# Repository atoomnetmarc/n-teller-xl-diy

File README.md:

**Status**: finished and working.

**Soldering and assembly time**: about 4 hours (if you can solder well).

# n-teller-xl-diy

n-teller-xl-diy is an IoT device that displays the number of [checked in participants and visitors](https://revspace.nl/N) at the hackerspace called [Revelation Space (or RevSpace)](https://revspace.nl).

It connects to the [RevSpace MQTT server](https://revspace.nl/MQTT) via WiFi using an ESP8266.

The MQTT server publishes to [a few topics of interest](https://revspace.nl/MQTT#Topics) that are subscribed:

- revspace/[doorduino](https://revspace.nl/Doorduino3)/checked-in: this is the current total of checked-in people.
- revspace/[state](https://revspace.nl/Spacestatus): the current state (open or closed) of the hackerspace.

# Schematic

[hardware/n-teller-xl-diy-schematic.pdf](hardware/n-teller-xl-diy-schematic.pdf)

# BOM

See interactive BOM: [hardware/bom/](https://html-preview.github.io/?url=https://github.com/atoomnetmarc/n-teller-xl-diy/blob/main/hardware/bom/ibom.html)

You will also need:

- The pcb. See [hardware/gerber/](hardware/gerber/) for gerber files. Order it at some PCB fabricator. You can also ask me for a bare PCB when I am at [RevSpace](https://revspace.nl/) hackerspace. I may have some left. I sell them for €5 a piece.
- 4x 3D prints of `7-segment 2.3 inch.stl` in opaque colored plastic. Use Gyroid infill for strong screw holes.
- 1x 3D print of `n-teller-xl-diy-stand.stl` in the color of your choice.
- 16x M2x10 self-tapping hex screws to mount the 4 7-segment 3D prints to the PCB.
- 3x M3x12 BHCS screws to mount the PCB to the 3D printed stand.
- About 28cm of 5cm wide vinyl white tape to stick onto the face of the 3D printed 7-segment digits. Or some other kind of 20x8cm thin white sticky plastic.

# Render

# Assembly

Last time I made assembly instructions for the [n-teller](https://github.com/atoomnetmarc/n-teller) at https://revspace.nl/N-teller, but that was not used, everybody just asked what to do, even after telling there are assembly instructions.

So for this one I won't make instructions. Just follow the BOM and look at the pictures on this page, and figure things out yourself.

Use a 5V power supply that can provide at least 1A.

# Firmware

Compile and flash the firmware located in the [firmware directory](firmware/). You will need [PlatformIO](https://platformio.org/) for this. I recommend installing the [PlatformIO extension for VSCode](https://platformio.org/install/ide?install=vscode).

# Configure WiFi

Double press the reset button (somewhat slowly). The letters `AP` will appear on the display. Now connect to a WiFi network with a name like `nteller-bcddc2895fd2`. Then goto: http://192.168.4.1/ and configure your WiFi.

# (Frequently) Asked Questions

> Do I really need the level shifter?
>
> -- <cite>User that does not know that the high signal level of 3.3V is lower than the VIH (3.5V) of the SK6812</cite>

Oh, sure, because nothing says "reliable electronics" like ignoring basic signal integrity! No, you don't *really* need the level shifter. Just blob some solder on `JP1` and cross your fingers that your 3.3V signals magically play nice with those finicky SK6812s. But when your display starts glitching like it's possessed by a deranged hacker, don't you dare come whining to me – after all, you're the self-proclaimed expert who thought this was a brilliant idea. Good luck with that masterpiece!

On serious note. It depends. I had 2 batches of SK6812 LEDS's. One batch worked on 3.3V DIN, but VCC must be below 5.1V, any higher and it did not work. The other batch did not work, even after lowering VCC to below 4.5V. So, yes, you need a level shifter.

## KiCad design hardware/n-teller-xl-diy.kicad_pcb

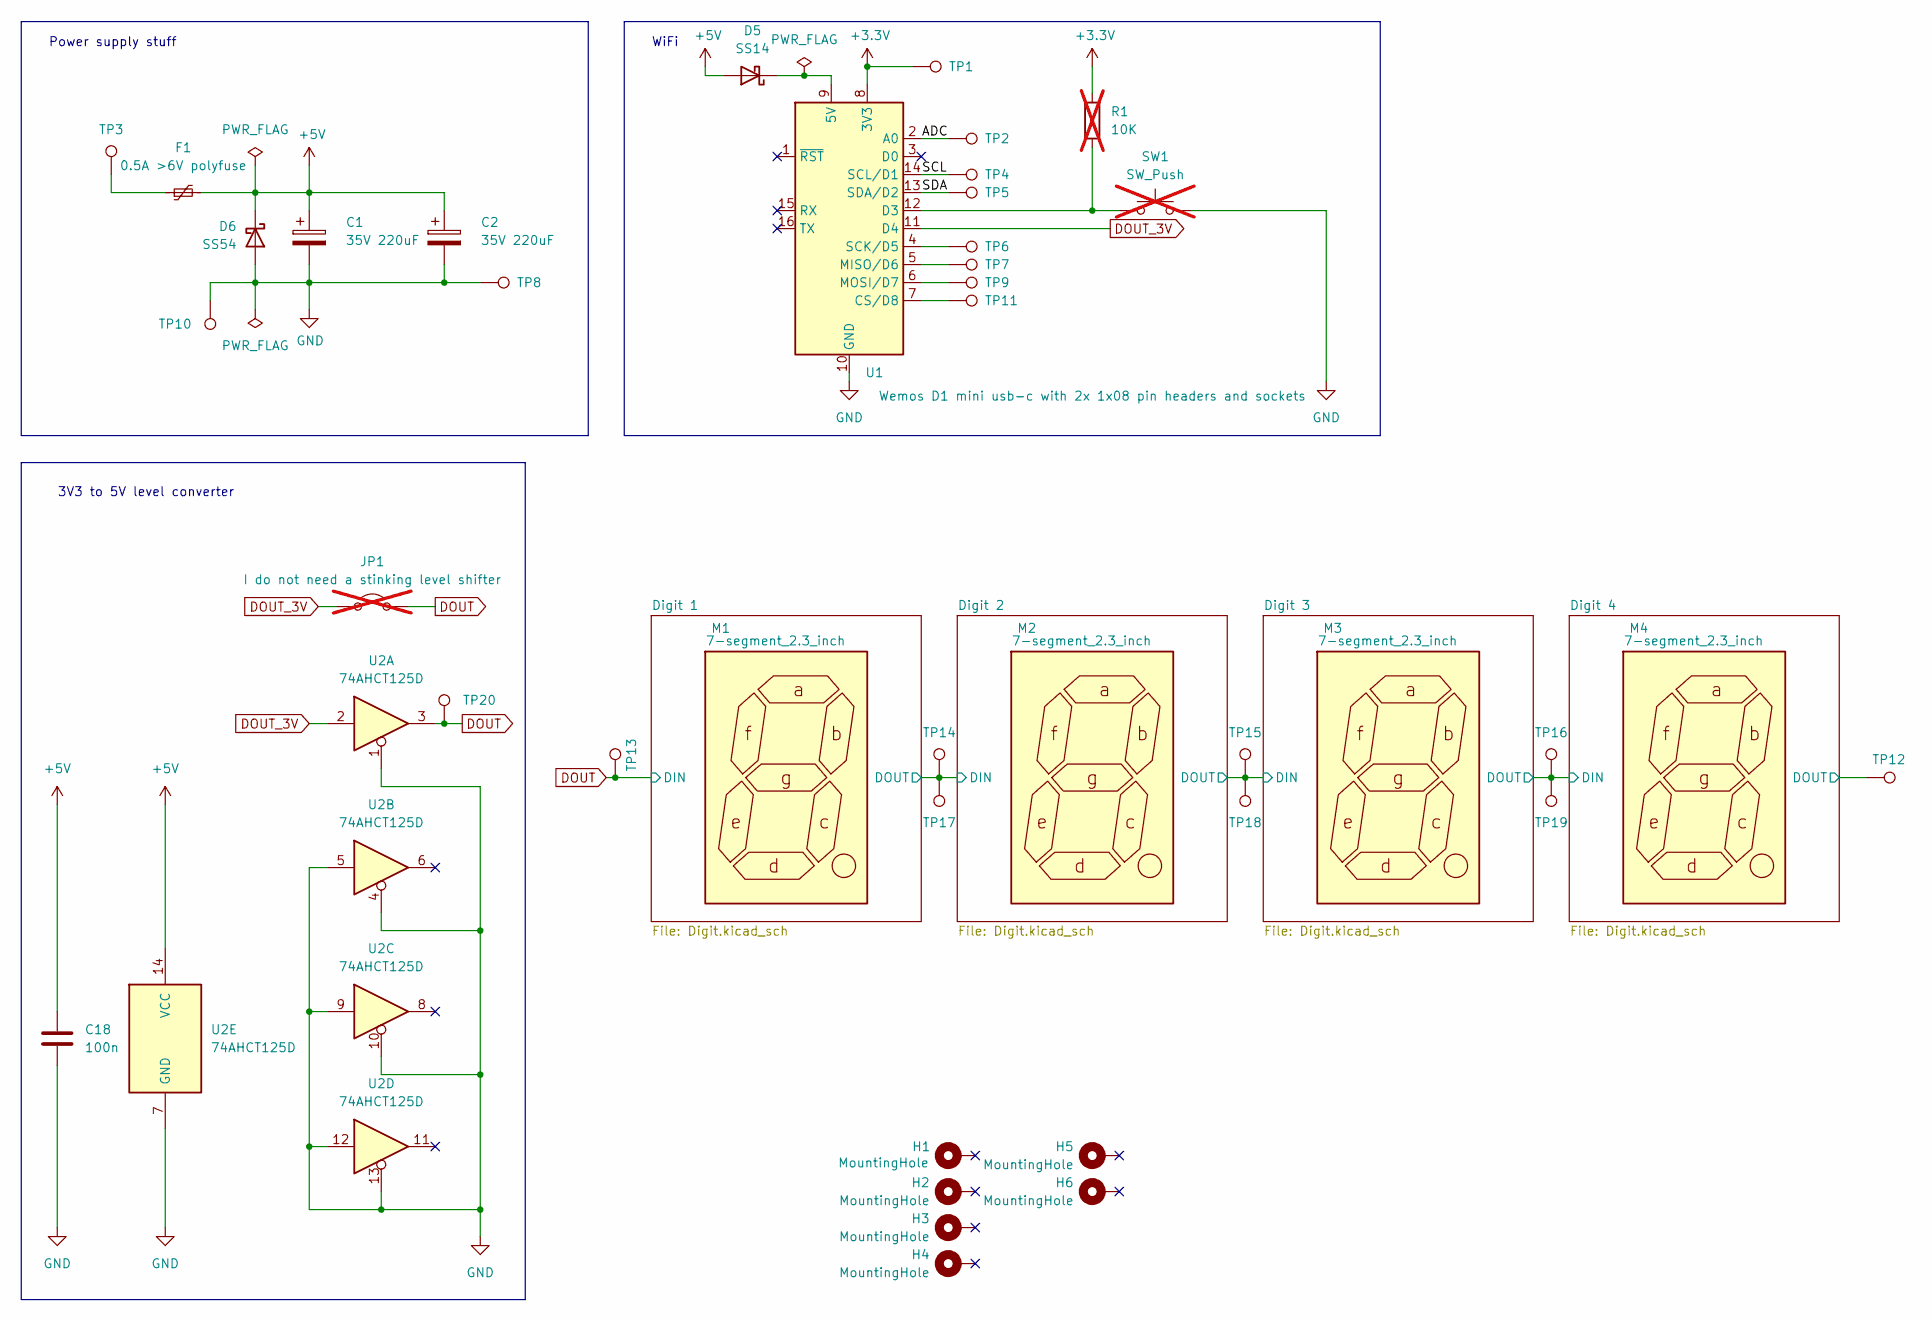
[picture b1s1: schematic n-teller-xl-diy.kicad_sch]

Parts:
C1, C2: 35V 220uF; CP_Radial_D10.0mm_P5.00mm
C18: 100n; C_0805_2012Metric_Pad1.18x1.45mm_HandSolder
D5: SS14; D_SMA
D6: SS54; D_SMA
F1: 0.5A >6V polyfuse; Fuse_1812_4532Metric_Pad1.30x3.40mm_HandSolder
H1, H2, H3, H4, H5, H6: MountingHole; MountingHole_3.2mm_M3_Pad_Via
JP1: I do not need a stinking level shifter; SolderJumper-2_P1.3mm_Open_TrianglePad1.0x1.5mm; not fitted
M1, M2, M3, M4: 7-segment_2.3_inch; 3d-printed 7-segment 2.3 inch
R1: 10K; R_0805_2012Metric_Pad1.20x1.40mm_HandSolder; not fitted
SW1: SW_Push; SW_SPST_CK_RS282G05A3; not fitted
TP1, TP2, TP8, TP12, TP13, TP14, TP15, TP16, TP17, TP18, TP19, TP20: TestPoint; TestPoint_Pad_D2.0mm
TP3, TP10: TestPoint; TestPoint_Pad_D4.0mm
TP4, TP5, TP6, TP7, TP9, TP11: TestPoint; TestPoint_Pad_D1.0mm
U1: Wemos D1 mini usb-c with 2x 1x08 pin headers and 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; WEMOS_D1_mini
U2: 74AHCT125D; SOIC-14_3.9x8.7mm_P1.27mm

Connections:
+3.3V: R1.2, TP1.1, U1.8 (3V3)
+5V: C1.1, C2.1, C18.1, D5.2 (A), D6.1 (K), F1.2, U2.14 (VCC); also elsewhere on the board
/ADC: TP2.1, U1.2 (A0)
/Digit 1/DOUT: TP14.1, TP17.1; also elsewhere on the board
/Digit 2/DOUT: TP15.1, TP18.1; also elsewhere on the board
/Digit 3/DOUT: TP16.1, TP19.1; also elsewhere on the board
/Digit 4/DOUT: TP12.1; also elsewhere on the board
/SCL: TP4.1, U1.14 (SCL/D1)
/SDA: TP5.1, U1.13 (SDA/D2)
DOUT: JP1.2 (B), TP13.1, TP20.1, U2.3; also elsewhere on the board
DOUT_3V: JP1.1 (A), U1.11 (D4), U2.2
GND: C1.2, C2.2, C18.2, D6.2 (A), SW1.1, TP8.1, TP10.1, U1.10 (GND), U2.1, U2.4, U2.5, U2.7 (GND), U2.9, U2.10, U2.12, U2.13; also elsewhere on the board
unnamed: D5.1 (K), U1.9 (5V)
unnamed: F1.1, TP3.1
unnamed: TP11.1, U1.7 (CS/D8)
unnamed: R1.1, SW1.2, U1.12 (D3)
unnamed: TP7.1, U1.5 (MISO/D6)
unnamed: TP9.1, U1.6 (MOSI/D7)
unnamed: TP6.1, U1.4 (SCK/D5)

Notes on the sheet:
WiFi
3V3 to 5V level converter
Power supply stuff

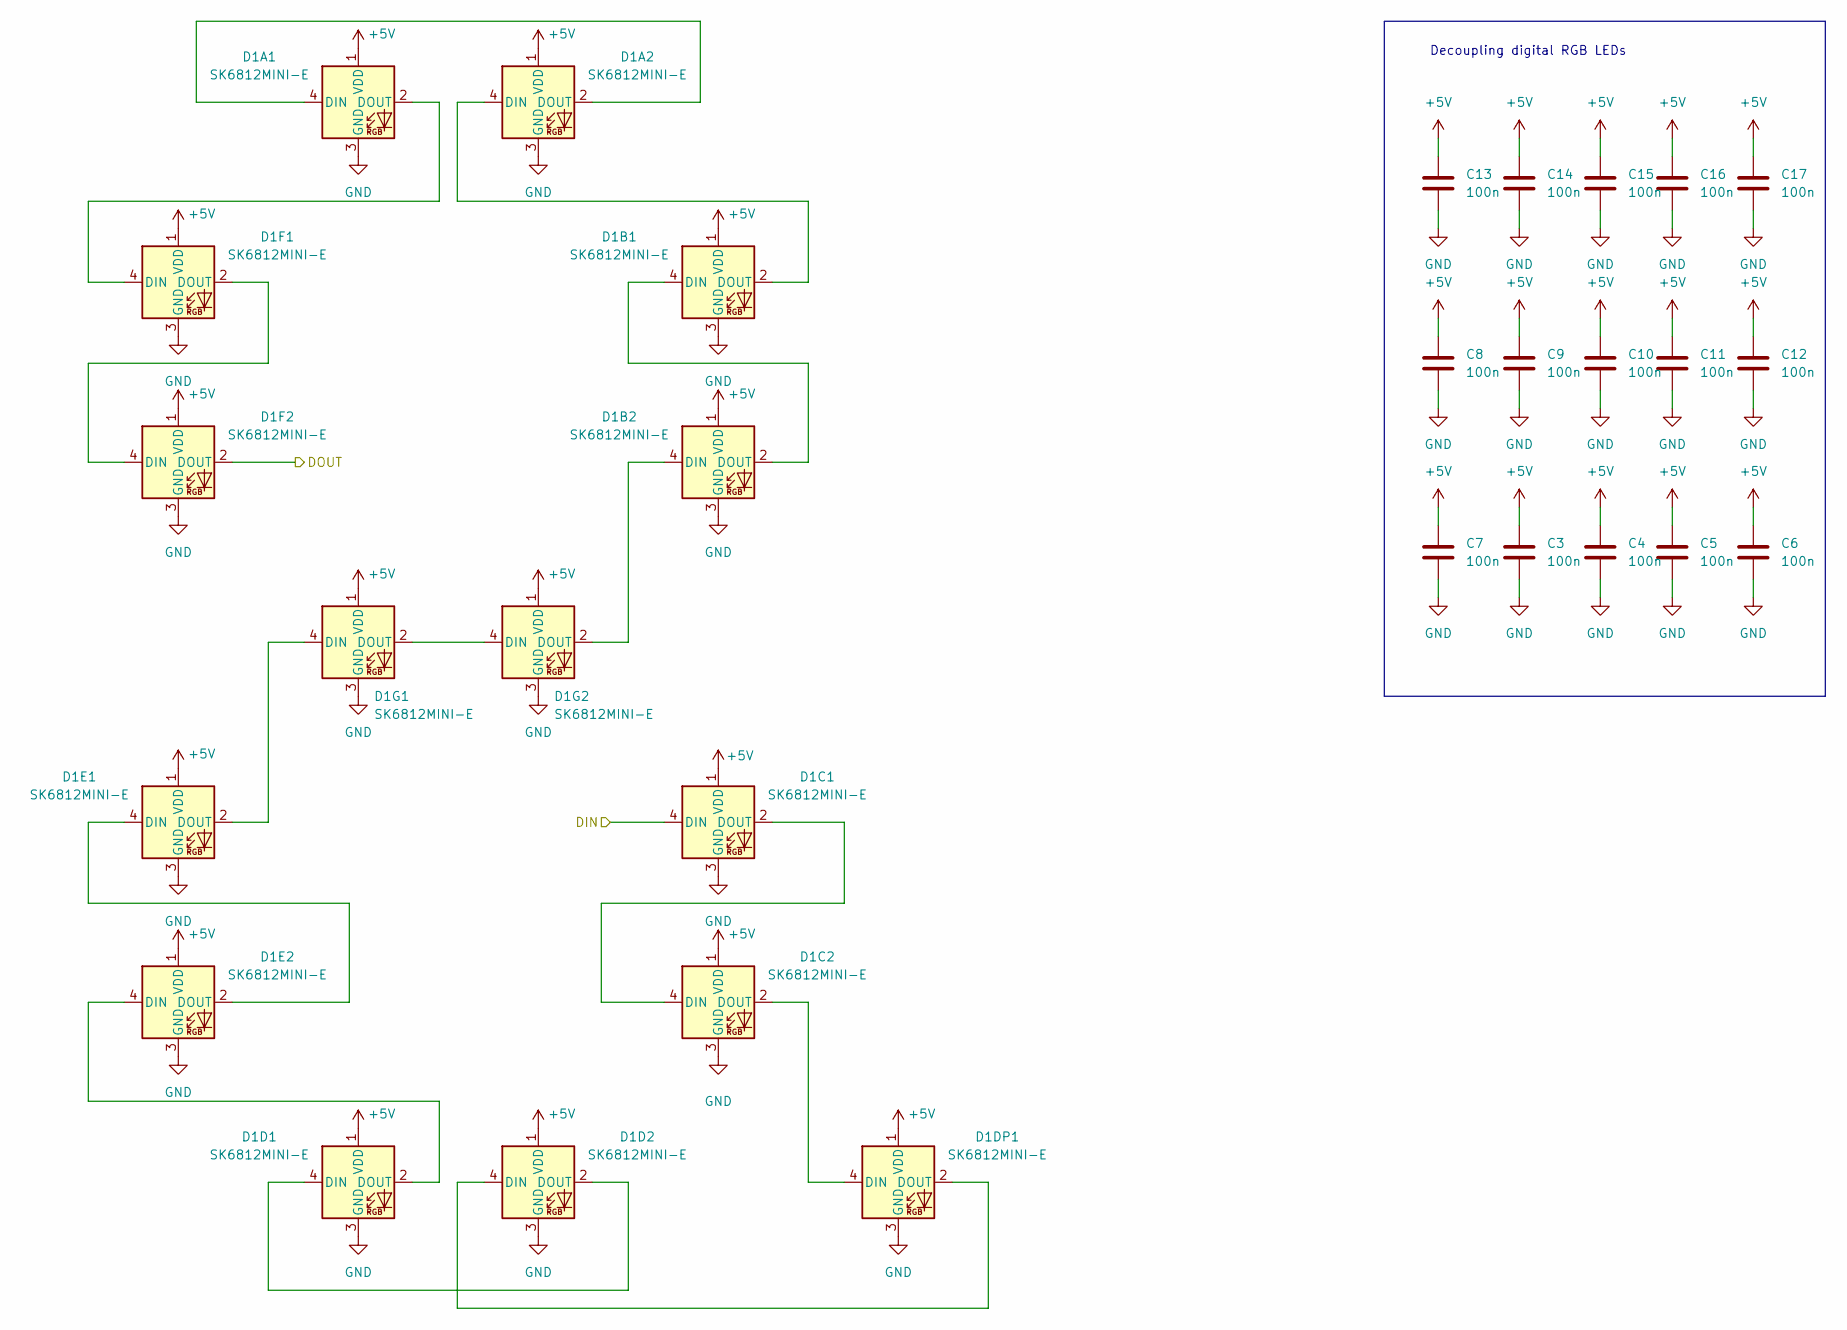
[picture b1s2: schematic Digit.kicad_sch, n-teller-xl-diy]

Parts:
C3, C4, C5, C6, C7, C8, C9, C10, C11, C12, C13, C14, C15, C16, C17: 100n; C_0805_2012Metric_Pad1.18x1.45mm_HandSolder
D1A1, D1A2, D1B1, D1B2, D1C1, D1C2, D1D1, D1D2, D1DP1, D1E1, D1E2, D1F1, D1F2, D1G1, D1G2: SK6812MINI-E; LED_SK6812MINI-E_3.2x2.8x1.78mm_P1.5mm

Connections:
+5V: C3.1, C4.1, C5.1, C6.1, C7.1, C8.1, C9.1, C10.1, C11.1, C12.1, C13.1, C14.1, C15.1, C16.1, C17.1, D1A1.1 (VDD), D1A2.1 (VDD), D1B1.1 (VDD), D1B2.1 (VDD), D1C1.1 (VDD), D1C2.1 (VDD), D1D1.1 (VDD), D1D2.1 (VDD), D1DP1.1 (VDD), D1E1.1 (VDD), D1E2.1 (VDD), D1F1.1 (VDD), D1F2.1 (VDD), D1G1.1 (VDD), D1G2.1 (VDD); also elsewhere on the board
/Digit 1/DOUT: D1F2.2 (DOUT); also elsewhere on the board
DOUT: D1C1.4 (DIN); also elsewhere on the board
GND: C3.2, C4.2, C5.2, C6.2, C7.2, C8.2, C9.2, C10.2, C11.2, C12.2, C13.2, C14.2, C15.2, C16.2, C17.2, D1A1.3 (GND), D1A2.3 (GND), D1B1.3 (GND), D1B2.3 (GND), D1C1.3 (GND), D1C2.3 (GND), D1D1.3 (GND), D1D2.3 (GND), D1DP1.3 (GND), D1E1.3 (GND), D1E2.3 (GND), D1F1.3 (GND), D1F2.3 (GND), D1G1.3 (GND), D1G2.3 (GND); also elsewhere on the board
unnamed: D1A1.4 (DIN), D1A2.2 (DOUT)
unnamed: D1A1.2 (DOUT), D1F1.4 (DIN)
unnamed: D1A2.4 (DIN), D1B1.2 (DOUT)
unnamed: D1B1.4 (DIN), D1B2.2 (DOUT)
unnamed: D1B2.4 (DIN), D1G2.2 (DOUT)
unnamed: D1C1.2 (DOUT), D1C2.4 (DIN)
unnamed: D1C2.2 (DOUT), D1DP1.4 (DIN)
unnamed: D1D1.4 (DIN), D1D2.2 (DOUT)
unnamed: D1D1.2 (DOUT), D1E2.4 (DIN)
unnamed: D1D2.4 (DIN), D1DP1.2 (DOUT)
unnamed: D1E1.4 (DIN), D1E2.2 (DOUT)
unnamed: D1E1.2 (DOUT), D1G1.4 (DIN)
unnamed: D1F1.2 (DOUT), D1F2.4 (DIN)
unnamed: D1G1.2 (DOUT), D1G2.4 (DIN)

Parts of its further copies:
C19, C20, C21, C22, C23, C24, C25, C26, C27, C28, C29, C30, C31, C32, C33, C34, C35, C36, C37, C38, C39, C40, C41, C42, C43, C44, C45, C46, C47, C48, C49, C50, C51, C52, C53, C54, C55, C56, C57, C58, C59, C60, C61, C62, C63: 100n; C_0805_2012Metric_Pad1.18x1.45mm_HandSolder
D2A1, D2A2, D2B1, D2B2, D2C1, D2C2, D2D1, D2D2, D2DP1, D2E1, D2E2, D2F1, D2F2, D2G1, D2G2, D3A1, D3A2, D3B1, D3B2, D3C1, D3C2, D3D1, D3D2, D3DP1, D3E1, D3E2, D3F1, D3F2, D3G1, D3G2, D4A1, D4A2, D4B1, D4B2, D4C1, D4C2, D4D1, D4D2, D4DP1, D4E1, D4E2, D4F1, D4F2, D4G1, D4G2: SK6812MINI-E; LED_SK6812MINI-E_3.2x2.8x1.78mm_P1.5mm

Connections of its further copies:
+5V: C19.1, C20.1, C21.1, C22.1, C23.1, C24.1, C25.1, C26.1, C27.1, C28.1, C29.1, C30.1, C31.1, C32.1, C33.1, C34.1, C35.1, C36.1, C37.1, C38.1, C39.1, C40.1, C41.1, C42.1, C43.1, C44.1, C45.1, C46.1, C47.1, C48.1, C49.1, C50.1, C51.1, C52.1, C53.1, C54.1, C55.1, C56.1, C57.1, C58.1, C59.1, C60.1, C61.1, C62.1, C63.1, D2A1.1 (VDD), D2A2.1 (VDD), D2B1.1 (VDD), D2B2.1 (VDD), D2C1.1 (VDD), D2C2.1 (VDD), D2D1.1 (VDD), D2D2.1 (VDD), D2DP1.1 (VDD), D2E1.1 (VDD), D2E2.1 (VDD), D2F1.1 (VDD), D2F2.1 (VDD), D2G1.1 (VDD), D2G2.1 (VDD), D3A1.1 (VDD), D3A2.1 (VDD), D3B1.1 (VDD), D3B2.1 (VDD), D3C1.1 (VDD), D3C2.1 (VDD), D3D1.1 (VDD), D3D2.1 (VDD), D3DP1.1 (VDD), D3E1.1 (VDD), D3E2.1 (VDD), D3F1.1 (VDD), D3F2.1 (VDD), D3G1.1 (VDD), D3G2.1 (VDD), D4A1.1 (VDD), D4A2.1 (VDD), D4B1.1 (VDD), D4B2.1 (VDD), D4C1.1 (VDD), D4C2.1 (VDD), D4D1.1 (VDD), D4D2.1 (VDD), D4DP1.1 (VDD), D4E1.1 (VDD), D4E2.1 (VDD), D4F1.1 (VDD), D4F2.1 (VDD), D4G1.1 (VDD), D4G2.1 (VDD); also elsewhere on the board
/Digit 1/DOUT: D2C1.4 (DIN); also elsewhere on the board
/Digit 2/DOUT: D2F2.2 (DOUT), D3C1.4 (DIN); also elsewhere on the board
/Digit 3/DOUT: D3F2.2 (DOUT), D4C1.4 (DIN); also elsewhere on the board
/Digit 4/DOUT: D4F2.2 (DOUT); also elsewhere on the board
GND: C19.2, C20.2, C21.2, C22.2, C23.2, C24.2, C25.2, C26.2, C27.2, C28.2, C29.2, C30.2, C31.2, C32.2, C33.2, C34.2, C35.2, C36.2, C37.2, C38.2, C39.2, C40.2, C41.2, C42.2, C43.2, C44.2, C45.2, C46.2, C47.2, C48.2, C49.2, C50.2, C51.2, C52.2, C53.2, C54.2, C55.2, C56.2, C57.2, C58.2, C59.2, C60.2, C61.2, C62.2, C63.2, D2A1.3 (GND), D2A2.3 (GND), D2B1.3 (GND), D2B2.3 (GND), D2C1.3 (GND), D2C2.3 (GND), D2D1.3 (GND), D2D2.3 (GND), D2DP1.3 (GND), D2E1.3 (GND), D2E2.3 (GND), D2F1.3 (GND), D2F2.3 (GND), D2G1.3 (GND), D2G2.3 (GND), D3A1.3 (GND), D3A2.3 (GND), D3B1.3 (GND), D3B2.3 (GND), D3C1.3 (GND), D3C2.3 (GND), D3D1.3 (GND), D3D2.3 (GND), D3DP1.3 (GND), D3E1.3 (GND), D3E2.3 (GND), D3F1.3 (GND), D3F2.3 (GND), D3G1.3 (GND), D3G2.3 (GND), D4A1.3 (GND), D4A2.3 (GND), D4B1.3 (GND), D4B2.3 (GND), D4C1.3 (GND), D4C2.3 (GND), D4D1.3 (GND), D4D2.3 (GND), D4DP1.3 (GND), D4E1.3 (GND), D4E2.3 (GND), D4F1.3 (GND), D4F2.3 (GND), D4G1.3 (GND), D4G2.3 (GND); also elsewhere on the board
unnamed: D2A1.4 (DIN), D2A2.2 (DOUT)
unnamed: D2A1.2 (DOUT), D2F1.4 (DIN)
unnamed: D2A2.4 (DIN), D2B1.2 (DOUT)
unnamed: D2B1.4 (DIN), D2B2.2 (DOUT)
unnamed: D2B2.4 (DIN), D2G2.2 (DOUT)
unnamed: D2C1.2 (DOUT), D2C2.4 (DIN)
unnamed: D2C2.2 (DOUT), D2DP1.4 (DIN)
unnamed: D2D1.4 (DIN), D2D2.2 (DOUT)
unnamed: D2D1.2 (DOUT), D2E2.4 (DIN)
unnamed: D2D2.4 (DIN), D2DP1.2 (DOUT)
unnamed: D2E1.4 (DIN), D2E2.2 (DOUT)
unnamed: D2E1.2 (DOUT), D2G1.4 (DIN)
unnamed: D2F1.2 (DOUT), D2F2.4 (DIN)
unnamed: D2G1.2 (DOUT), D2G2.4 (DIN)
unnamed: D3A1.4 (DIN), D3A2.2 (DOUT)
unnamed: D3A1.2 (DOUT), D3F1.4 (DIN)
unnamed: D3A2.4 (DIN), D3B1.2 (DOUT)
unnamed: D3B1.4 (DIN), D3B2.2 (DOUT)
unnamed: D3B2.4 (DIN), D3G2.2 (DOUT)
unnamed: D3C1.2 (DOUT), D3C2.4 (DIN)
unnamed: D3C2.2 (DOUT), D3DP1.4 (DIN)
unnamed: D3D1.4 (DIN), D3D2.2 (DOUT)
unnamed: D3D1.2 (DOUT), D3E2.4 (DIN)
unnamed: D3D2.4 (DIN), D3DP1.2 (DOUT)
unnamed: D3E1.4 (DIN), D3E2.2 (DOUT)
unnamed: D3E1.2 (DOUT), D3G1.4 (DIN)
unnamed: D3F1.2 (DOUT), D3F2.4 (DIN)
unnamed: D3G1.2 (DOUT), D3G2.4 (DIN)
unnamed: D4A1.4 (DIN), D4A2.2 (DOUT)
unnamed: D4A1.2 (DOUT), D4F1.4 (DIN)
unnamed: D4A2.4 (DIN), D4B1.2 (DOUT)
unnamed: D4B1.4 (DIN), D4B2.2 (DOUT)
unnamed: D4B2.4 (DIN), D4G2.2 (DOUT)
unnamed: D4C1.2 (DOUT), D4C2.4 (DIN)
unnamed: D4C2.2 (DOUT), D4DP1.4 (DIN)
unnamed: D4D1.4 (DIN), D4D2.2 (DOUT)
unnamed: D4D1.2 (DOUT), D4E2.4 (DIN)
unnamed: D4D2.4 (DIN), D4DP1.2 (DOUT)
unnamed: D4E1.4 (DIN), D4E2.2 (DOUT)
unnamed: D4E1.2 (DOUT), D4G1.4 (DIN)
unnamed: D4F1.2 (DOUT), D4F2.4 (DIN)
unnamed: D4G1.2 (DOUT), D4G2.4 (DIN)

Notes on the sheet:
Decoupling digital RGB LEDs

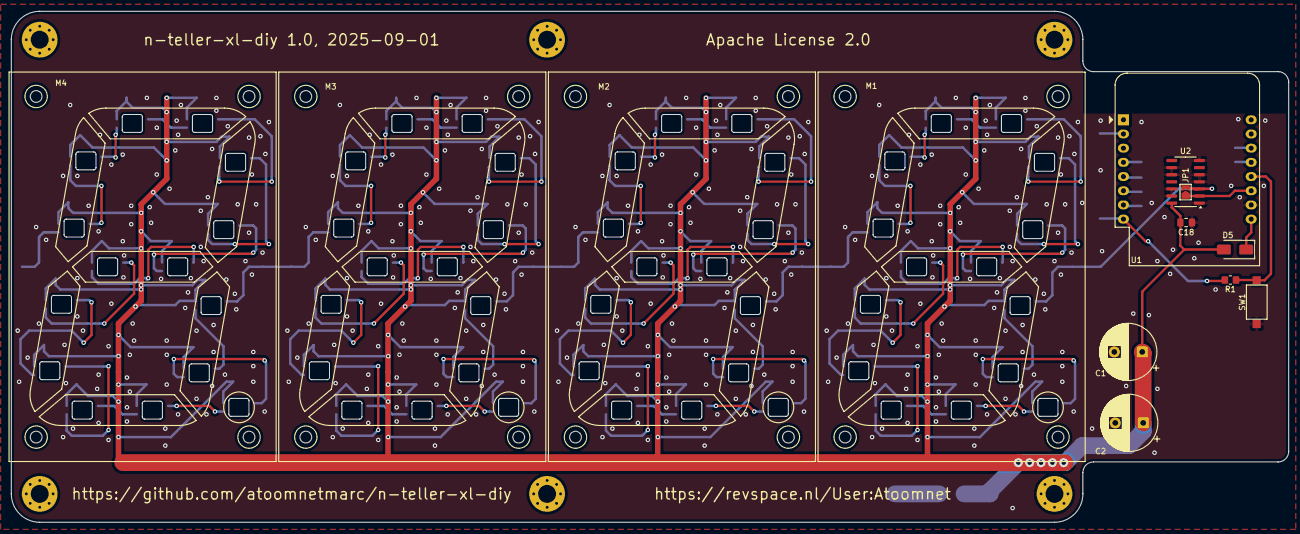
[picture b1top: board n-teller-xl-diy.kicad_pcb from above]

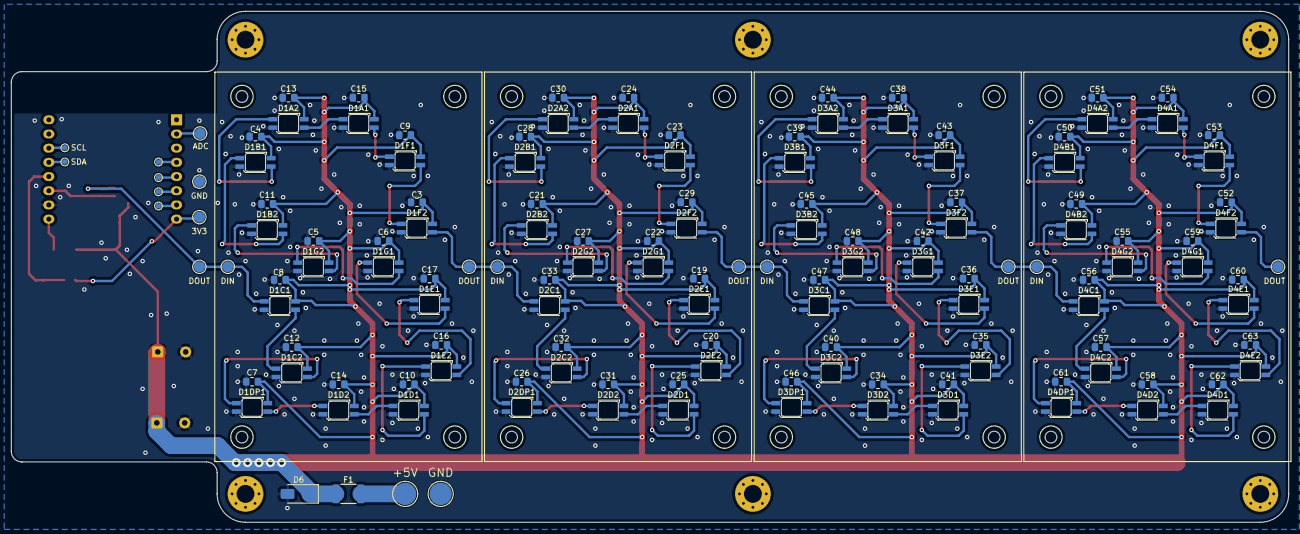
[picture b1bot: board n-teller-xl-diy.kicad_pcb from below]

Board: 2 copper layers, 228.6 x 91.4 mm, 161 parts (143 on the bottom side), 75 nets.

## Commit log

2025-09-18 Add level shifter note.
2025-09-18 Add startup LED debug patterns.
2025-09-19 Make ibom viewable in browser.
2025-09-21 3d-print hint.
2025-09-21 Add optional 3d-printable diffuser.
2025-09-23 Enlarge m2x10 holes from 1.5mm to 1.9mm.
2026-01-23 Add CONTRIBUTING.md

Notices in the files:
README.md:
License: Apache 2.0
hardware/Digit.kicad_sch:
Apache License 2.0
